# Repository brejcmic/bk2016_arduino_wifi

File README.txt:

Arduino project
Student: Poznicek

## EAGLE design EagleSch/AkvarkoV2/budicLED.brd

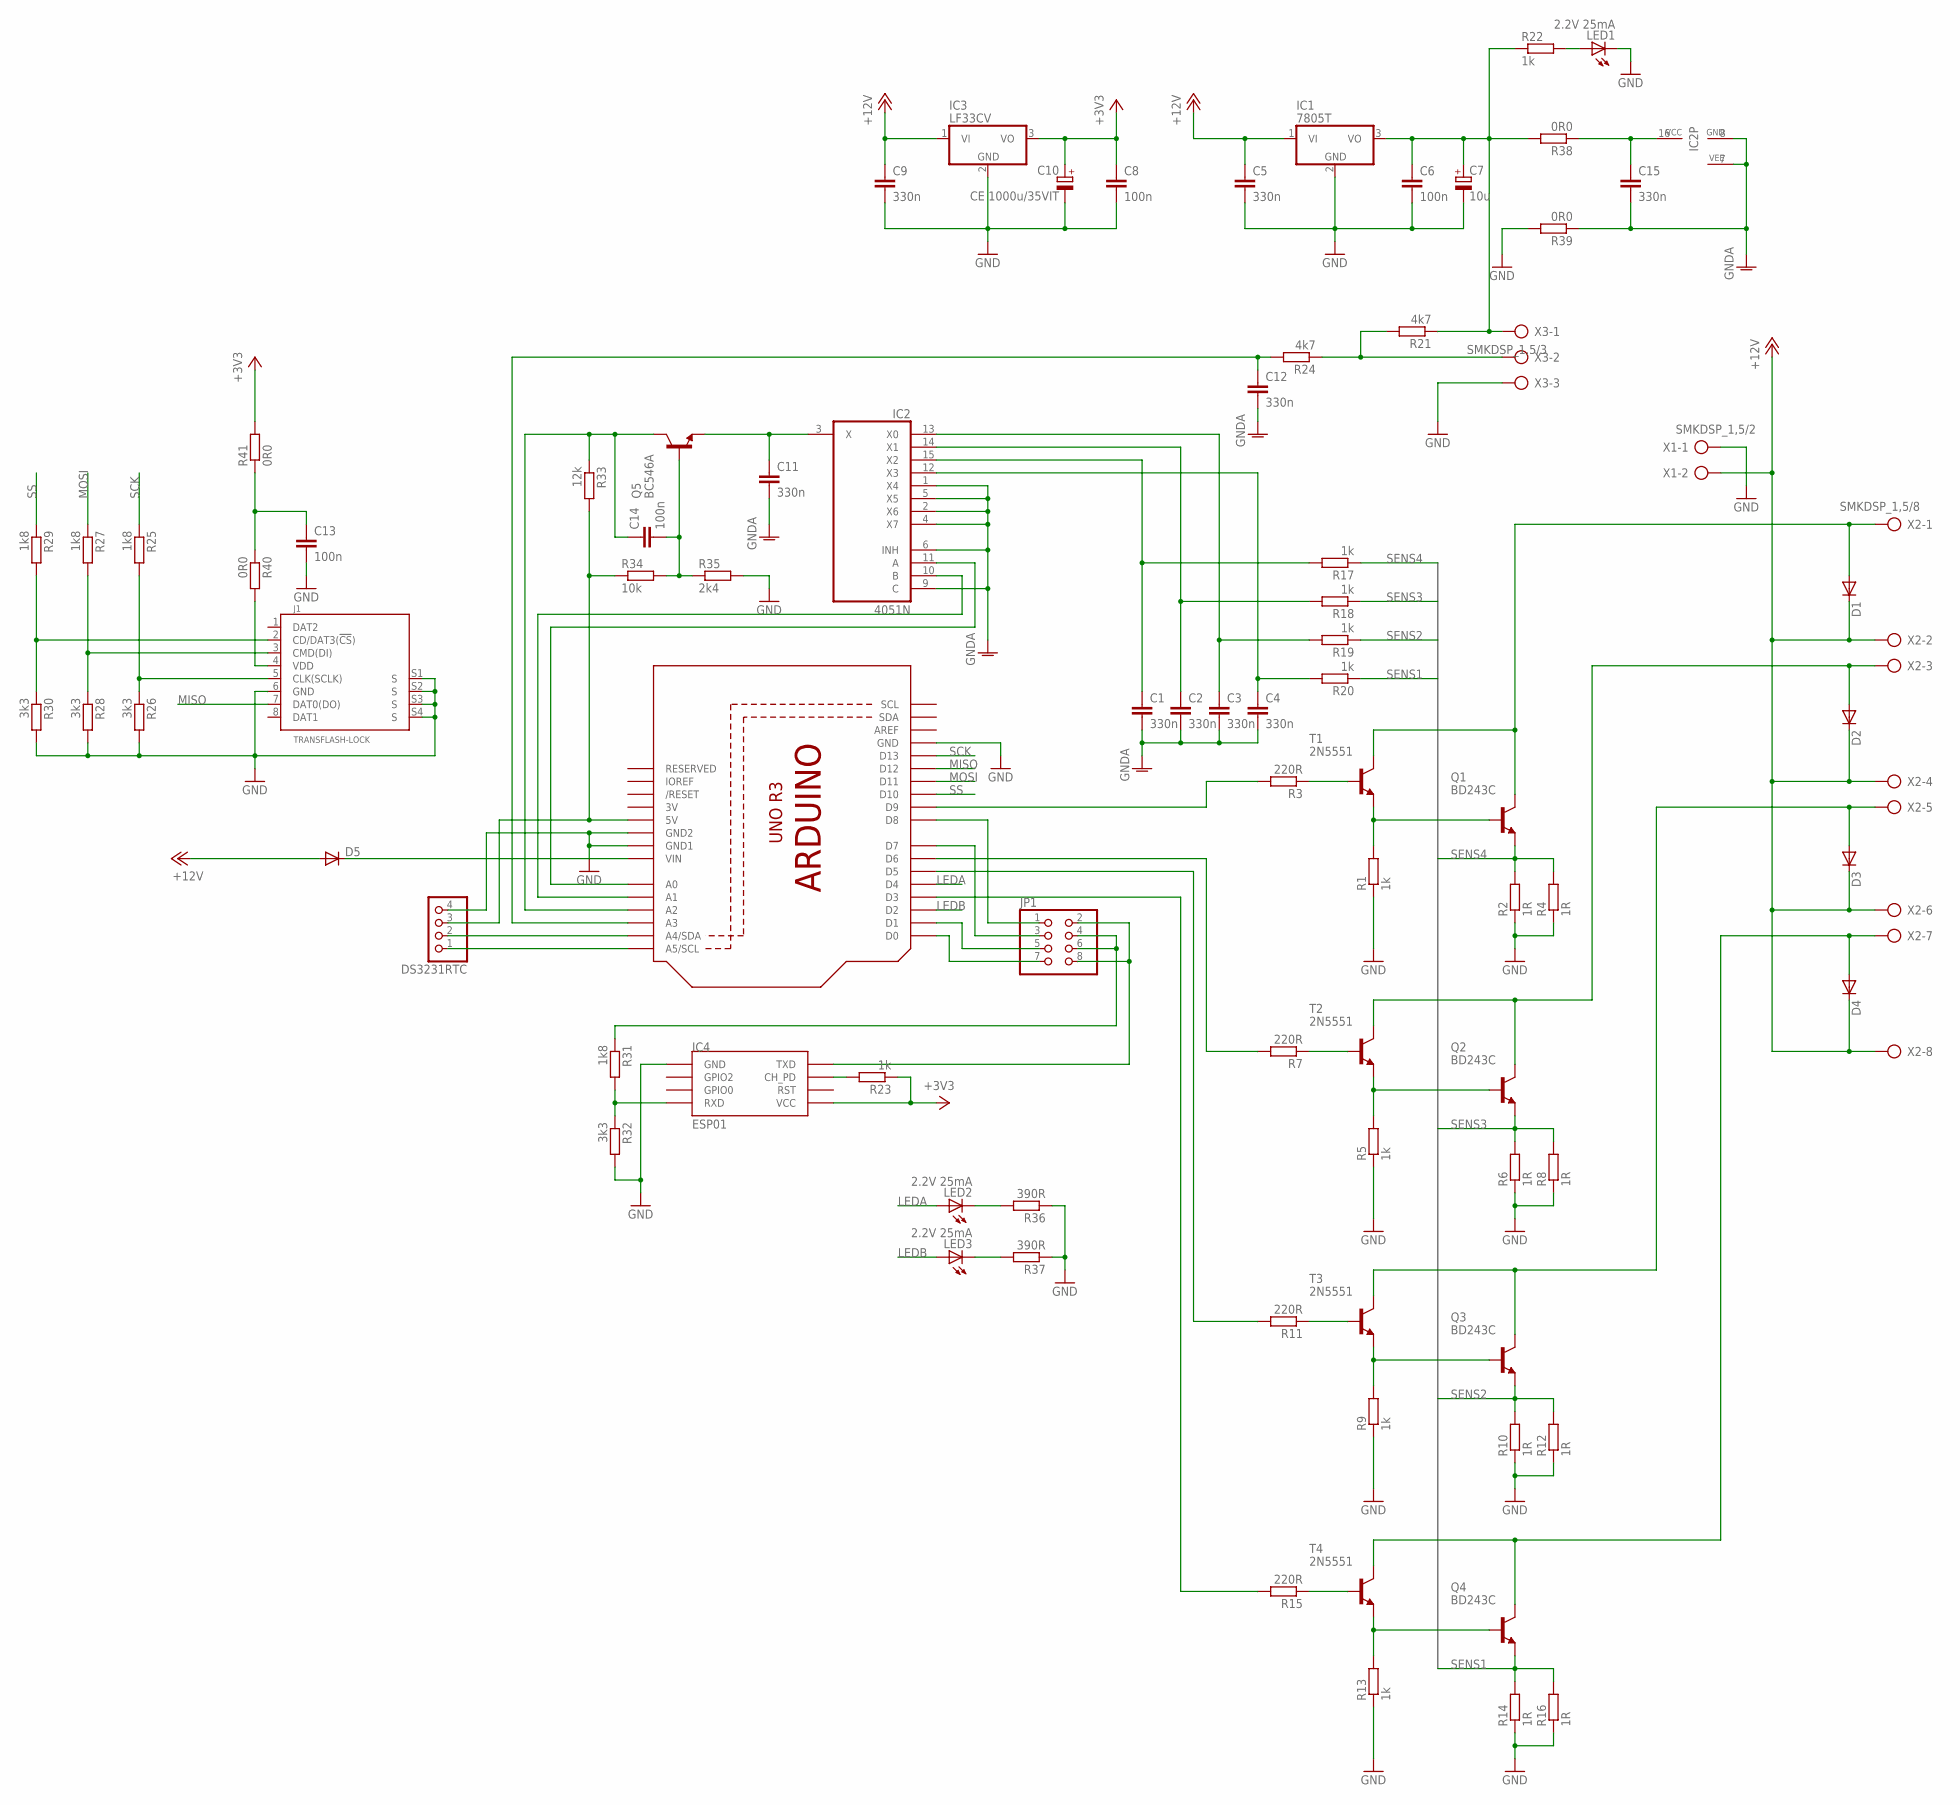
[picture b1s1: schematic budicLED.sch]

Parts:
C1, C2, C3, C4, C5, C9, C11, C12, C15: 330n; C1206K
C6, C8, C13, C14: 100n; C1206K
C7: 10u; E5-10,5
C10: CE 1000u/35VIT; E5-10,5
D1, D2, D3, D4: DIODE-DO201-15; DO201-15
D5: DIODE-MELF-MLL41; MELF-MLL41
DS3231RTC: PINHD-1X4; 1X04
IC1: 7805T; TO220H
IC2: 4051N; DIL16
IC3: LF33CV; TO220H
IC4: ESP01
J1: TRANSFLASH-LOCK; TRANSFLASH-LOCK-SOCK
JP1: PINHD-2X4; 2X04
LED1, LED2, LED3: 2.2V 25mA; LED3MM
Q1, Q2, Q3, Q4: BD243C; TO220
Q5: BC546A; TO92-EBC
R1, R5, R9, R13: 1k; 0207/12
R2, R4, R6, R8, R10, R12, R14, R16: 1R; 0411/15
R3, R7, R11, R15: 220R; 0207/12
R17, R18, R19, R20, R22, R23: 1k; R0805
R21: 4k7; 0207/12
R24: 4k7; 0207/15
R25, R27, R29, R31: 1k8; 0207/12
R26, R28, R30, R32: 3k3; 0207/12
R33: 12k; 0207/12
R34: 10k; 0207/12
R35: 2k4; 0207/12
R36, R37: 390R; 0207/12
R38: 0R0; 0207/15
R39, R40, R41: 0R0; 0207/12
T1, T2, T3, T4: 2N5551; TO92-CBE
U1: ARDUINOR3-DIMENSION; ARDUINOR3
X1: SMKDSP_1,5/2
X2: SMKDSP_1,5/8
X3: SMKDSP_1,5/3

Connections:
3V: U1.3V
+3V3: C8.1, C10.+, IC3.3 (VO), IC4.VCC, R23.1, R41.2
+12V: C5.1, C9.1, D1.C, D2.C, D3.C, D4.C, D5.A, IC1.1 (VI), IC3.1 (VI), X1.2, X2.2, X2.4, X2.6, X2.8
GND: C5.2, C6.2, C7.-, C8.2, C9.2, C10.-, C13.2, DS3231RTC.4, IC1.2 (GND), IC3.2 (GND), IC4.GND, J1.6 (GND), J1.S1 (S), J1.S2 (S), J1.S3 (S), J1.S4 (S), LED1.K (C), R1.1, R2.1, R4.1, R5.1, R6.1, R8.1, R9.1, R10.1, R12.1, R13.1, R14.1, R16.1, R26.2, R28.2, R30.2, R32.2, R35.2, R36.1, R37.1, R39.2, U1.GND, U1.GND1, U1.GND2, X1.1, X3.3
GNDA: C1.2, C2.2, C3.2, C4.2, C11.2, C12.2, C15.2, IC2.1 (X4), IC2.2 (X6), IC2.4 (X7), IC2.5 (X5), IC2.6 (INH), IC2.7 (VEE), IC2.8 (GND), IC2.9 (C), R39.1
LEDA: LED2.A, U1.D4
LEDB: LED3.A, U1.D2
MISO: J1.7 (DAT0(DO)), U1.D12
MOSI: R27.1, U1.D11
unnamed: Q1.1 (B), R1.2, T1.E
unnamed: D1.A, Q1.2 (C), T1.C, X2.1
unnamed: R3.1, T1.B
unnamed: D2.A, Q2.2 (C), T2.C, X2.3
unnamed: D3.A, Q3.2 (C), T3.C, X2.5
unnamed: Q2.1 (B), R5.2, T2.E
unnamed: D4.A, Q4.2 (C), T4.C, X2.7
unnamed: R7.1, T2.B
unnamed: Q3.1 (B), R9.2, T3.E
unnamed: R21.2, R24.1, X3.2
unnamed: R11.1, T3.B
unnamed: Q4.1 (B), R13.2, T4.E
unnamed: DS3231RTC.1, U1.A5 (A5/SCL)
unnamed: R15.1, T4.B
unnamed: R11.2, U1.D5
unnamed: R3.2, U1.D9
unnamed: IC4.CH_PD, R23.2
unnamed: C14.1, Q5.C, R33.1, U1.A2
unnamed: C14.2, Q5.B, R34.2, R35.1
unnamed: IC4.TX (TXD), JP1.2, JP1.8
unnamed: C12.1, R24.2, U1.A3
unnamed: R7.2, U1.D6
unnamed: C6.1, C7.+, IC1.3 (VO), R21.1, R22.1, R38.2, X3.1
unnamed: DS3231RTC.2, U1.A4 (A4/SDA)
unnamed: JP1.4, JP1.6, R31.1
unnamed: IC2.11 (A), U1.A0
unnamed: LED1.A, R22.2
unnamed: JP1.3, U1.D7
unnamed: C1.1, IC2.15 (X2), R17.2
unnamed: C2.1, IC2.14 (X1), R18.2
unnamed: C3.1, IC2.13 (X0), R19.2
unnamed: J1.5 (CLK(SCLK)), R25.2, R26.1
unnamed: C4.1, IC2.12 (X3), R20.2
unnamed: IC2.10 (B), U1.A1
unnamed: R15.2, U1.D3
unnamed: J1.3 (CMD(DI)), R27.2, R28.1
unnamed: J1.2 (CD/DAT3(!CS!)), R29.2, R30.1
unnamed: JP1.5, U1.D1
unnamed: IC4.RX (RXD), R31.2, R32.1
unnamed: C11.1, IC2.3 (X), Q5.E
unnamed: JP1.7, U1.D0
unnamed: JP1.1, U1.D8
unnamed: LED2.K (C), R36.2
unnamed: DS3231RTC.3, R33.2, R34.1, U1.5V
unnamed: LED3.K (C), R37.2
unnamed: C15.1, IC2.16 (VCC), R38.1
unnamed: J1.4 (VDD), R40.2
unnamed: D5.C, U1.VIN
unnamed: C13.1, R40.1, R41.1
SCK: R25.1, U1.D13
SENS1: Q4.3 (E), R14.2, R16.2, R20.1
SENS2: Q3.3 (E), R10.2, R12.2, R19.1
SENS3: Q2.3 (E), R6.2, R8.2, R18.1
SENS4: Q1.3 (E), R2.2, R4.2, R17.1
SS: R29.1, U1.D10

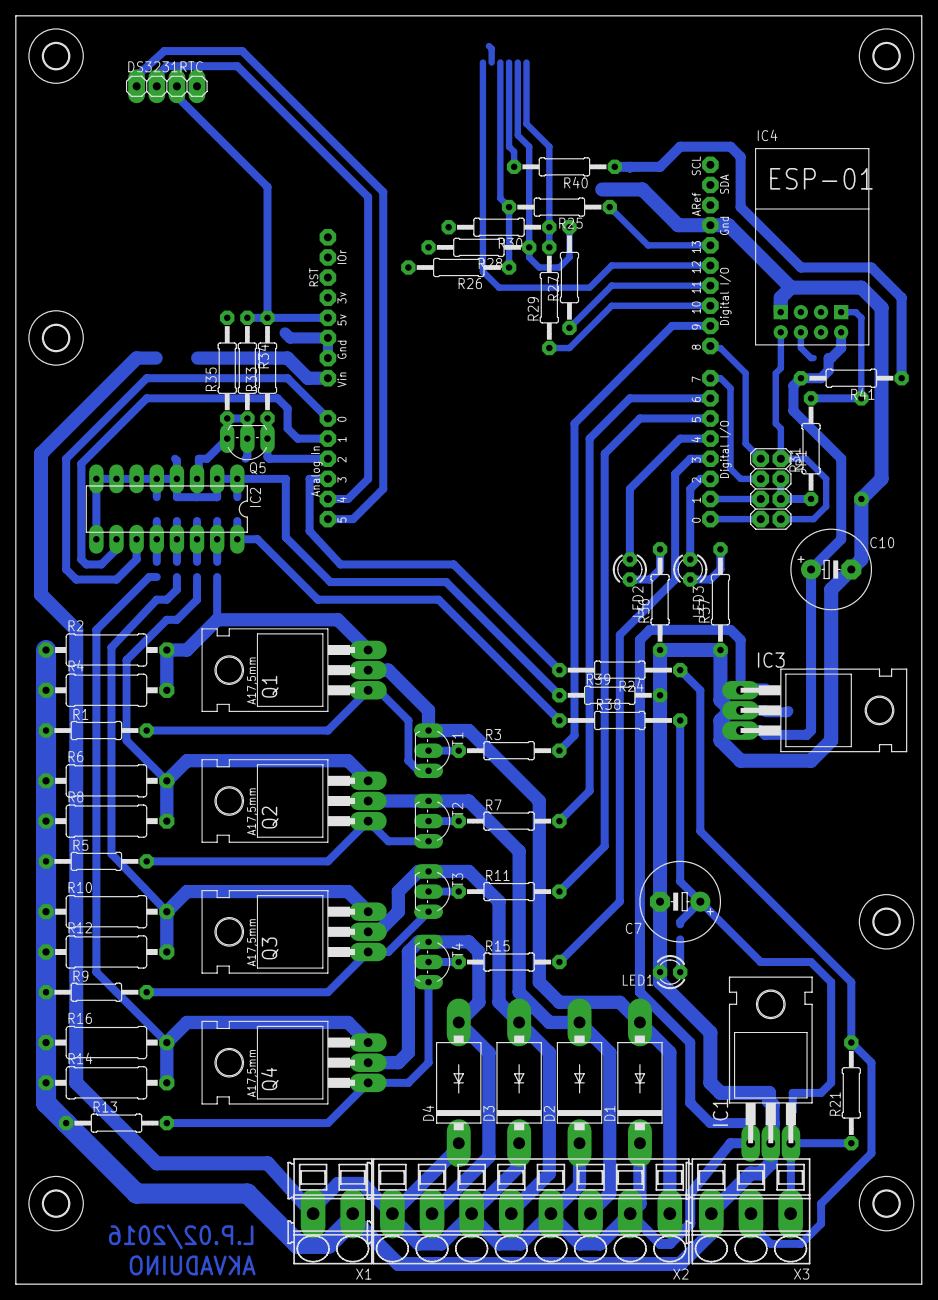
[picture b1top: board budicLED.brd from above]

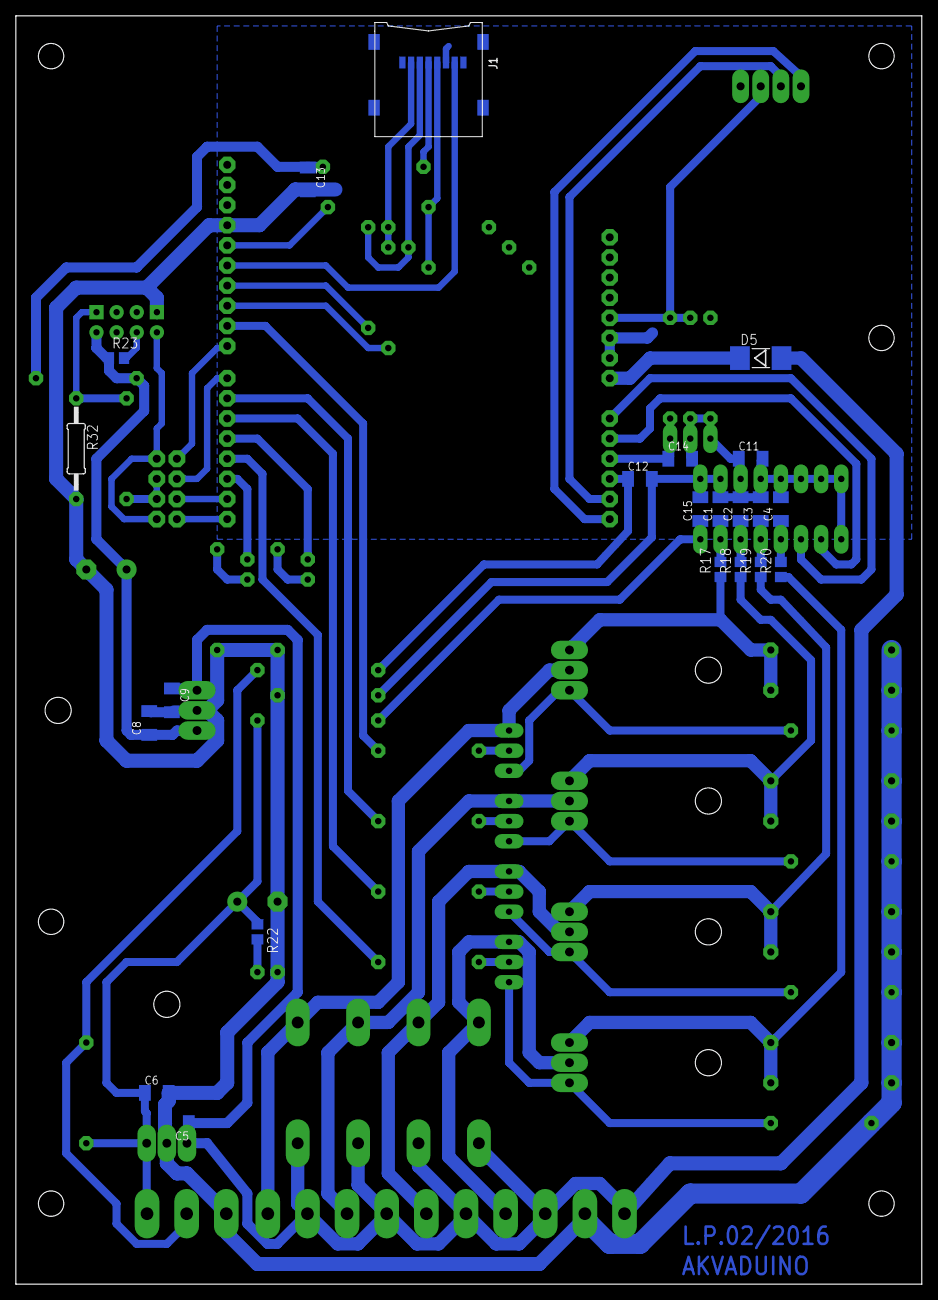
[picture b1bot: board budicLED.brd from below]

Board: 2 copper layers, 114.3 x 160.0 mm, 90 parts (22 on the bottom side), 63 nets.

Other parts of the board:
U$1, U$2, U$3, U$4, U$5, U$6: 3,2

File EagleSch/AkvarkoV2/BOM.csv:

"Qty";"Value";"Device";"Package";"Parts";"Description";"";
"4";"";"DIODE-DO201-15";"DO201-15";"D1, D2, D3, D4";"DIODE";"";
"1";"";"PINHD-1X4";"1X04";"DS3231RTC";"PIN HEADER";"";
"1";"";"PINHD-2X4";"2X04";"JP1";"PIN HEADER";"";
"3";"0R0";"R-EU_0207/12";"0207/12";"R39, R40, R41";"RESISTOR, European symbol";"";
"1";"0R0";"R-EU_0207/15";"0207/15";"R38";"RESISTOR, European symbol";"";
"4";"100n";"C-EUC1206K";"C1206K";"C6, C8, C9, C13";"CAPACITOR, European symbol";"";
"3";"10k";"R-EU_0207/12";"0207/12";"R33, R34, R35";"RESISTOR, European symbol";"";
"1";"10u";"CPOL-EUE5-10.5";"E5-10,5";"C7";"POLARIZED CAPACITOR, European symbol";"";
"8";"1R";"R-EU_0411/15";"0411/15";"R2, R4, R6, R8, R10, R12, R14, R16";"RESISTOR, European symbol";"";
"4";"1k";"R-EU_0207/12";"0207/12";"R1, R5, R9, R13";"RESISTOR, European symbol";"";
"4";"1k";"R-EU_R0805";"R0805";"R17, R18, R19, R20";"RESISTOR, European symbol";"";
"4";"1k8";"R-EU_0207/12";"0207/12";"R25, R27, R29, R31";"RESISTOR, European symbol";"";
"3";"2.2V 25mA";"LED3MM";"LED3MM";"LED1, LED2, LED3";"LED";"";
"4";"220R";"R-EU_0207/12";"0207/12";"R3, R7, R11, R15";"RESISTOR, European symbol";"";
"4";"2N5551";"2N5551-NPN-TO92-CBE";"TO92-CBE";"T1, T2, T3, T4";"NPN Transistror";"";
"9";"330n";"C-EUC1206K";"C1206K";"C1, C2, C3, C4, C5, C11, C12, C14, C15";"CAPACITOR, European symbol";"";
"2";"390R";"R-EU_0207/12";"0207/12";"R36, R37";"RESISTOR, European symbol";"";
"1";"390R";"R-EU_R0805";"R0805";"R22";"RESISTOR, European symbol";"";
"4";"3k3";"R-EU_0207/12";"0207/12";"R26, R28, R30, R32";"RESISTOR, European symbol";"";
"1";"4051N";"4051N";"DIL16";"IC2";"8-channel ANALOG MULTIPLEXER";"";
"1";"4k7";"R-EU_0207/12";"0207/12";"R21";"RESISTOR, European symbol";"";
"1";"4k7";"R-EU_0207/15";"0207/15";"R24";"RESISTOR, European symbol";"";
"1";"4k7";"R-EU_R0805";"R0805";"R23";"RESISTOR, European symbol";"";
"1";"7805T";"7805T";"TO220H";"IC1";"Positive VOLTAGE REGULATOR";"";
"1";"ARDUINOR3-DIMENSION";"ARDUINOR3-DIMENSION";"ARDUINOR3";"U1";"This is a new object for the new Arduino R3 - with extra pins that you may want to use (such as IOref, and duplicated A4/A5";"";
"1";"BC546A";"BC546A";"TO92-EBC";"Q5";"NPN Transistor";"";
"4";"BD243C";"-NPN-TO220";"TO220";"Q1, Q2, Q3, Q4";"NPN Transistror";"";
"1";"CE 1000u/35VIT";"CPOL-EUE5-10.5";"E5-10,5";"C10";"POLARIZED CAPACITOR, European symbol";"";
"1";"ESP01";"ESP01";"ESP01";"IC4";"ESP8266 Wifi module 01";"";
"1";"LF33CV";"7805T";"TO220H";"IC3";"Positive VOLTAGE REGULATOR";"";
"1";"SMKDSP_1,5/2";"SMKDSP_1,5/2";"SMKDSP_1,5/2";"X1";"Printklemme, Nennstrom: 17,5 A, Bemessungsspannung: 250 V, Raster: 5,0 mm";"";
"1";"SMKDSP_1,5/3";"SMKDSP_1,5/3";"SMKDSP_1,5/3";"X3";"Printklemme, Nennstrom: 17,5 A, Bemessungsspannung: 250 V, Raster: 5,0 mm";"";
"1";"SMKDSP_1,5/8";"SMKDSP_1,5/8";"SMKDSP_1,5/8";"X2";"Printklemme, Nennstrom: 17,5 A, Bemessungsspannung: 250 V, Raster: 5,0 mm";"";
"1";"TRANSFLASH-LOCK";"TRANSFLASH-LOCK";"TRANSFLASH-LOCK-SOCK";"J1";"TransFlash TF Micro SD Card Socket Adapter";"";

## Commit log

2016-03-14 Poznamka v README
2016-03-14 Manualy a zaklad seriove komunikace
2016-03-14 Pridano vraceni html stranky.
2016-03-15 Funkcni kod. Lze se pripojit na zarizeni pres web browser. Na obrazovce se vypise Ahoj.
2016-03-16 Pridan priklad html stranky od Honzy
2016-03-17 Zmena vykreslovani webovky, odzkouseno. Zapis webu do String.
2016-03-17 Rozpracovano nasobne vraceni ruznych webovych stranek
2016-03-18 Funkcni kod, ktery pres webovy prohlizec rozsveci a zhasina ledku na pinu 7.
2016-03-18 Stranky byly pojmenovany pomoci enum.
2016-03-21 Rozpracovany stavovy automat odesilani html stranky.
2016-03-22 Stale nefunguje odesilani stranky. Velikost pameti vyhovuje.
2016-03-23 Konecne trochu funkcni htmlMonitor.
2016-03-23 htmlMonitor je plne funkcni. Lze odesilat stranku do velikosti 2k. Odzkouseno
2016-03-24 - predelano casovani udalosti, nyni pomoci "com_delay" - doplneny ochrany jako WATCHDOG - smazany prebytecne lokalni promenne - prejmenovany funkce monitoru - odzkouseno, funkcni
2016-03-24 Pridan popis HTTP 1.1
2016-03-26 Zmenena funkce nalezeni retezce. Nyni se retezec hleda v poslednich 8 znacich.
2016-03-27 Funkcni servisni log a predelana koncepce hledani retezcu. Vystup obou seriovych linek se zapisuje do FIFO, ve kterem se nasledne hleda retezec.
2016-03-28 Predelana inicializace pripojeni k wifi siti. Inicializace rozdelena do dvou funkci, ktere lze volat samostatne. Prvni inicializuje servisni linku, druha inicializuje komunikaci s esp8266. Odzkouseno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
2016-03-28 Funkcni rozdelelni zpravy do vice paketu.
2016-03-30 Verze zakladove desky akvaduino pred upravami
2016-03-30 Pridan slot pro SD kartu, odstraneny signalizacni diody.
2016-03-31 Přidán datasheet ESP8266
2016-03-31 Na DPS: - upraveno napajeni - zmenena pouzdra rezistoru u SD karty - seriova linka vyvedena na kolikovou listu - zvetsena sirka spoje GND, doplnen jeden filtracni kapacitor k SD slotu
2016-03-31 DPS pred vyrobou, nutna kontrola rozmeru.
2016-04-01 DPS: - pridany LED, - dratove propojky nahrazeny reszistory 0R0, - doplnena rozlita med, - pridan zesilovaci prvek (tranzistor) k AD prevodnikum od snimani proudu ve vykonovem obvodu, - pridano nekol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
2016-04-01 DPS: - posilena tloustka vykonove zeme a privodu napajeni k Arduino UNO
2016-04-02 DPS: - RTC modul obracen o 90°, jinak se nevejde do krabicky.
2016-04-02 Pripravena vyrobni data.
2016-04-05 Doplnen BOM
2016-04-06 DPS: - vytvorena objednavka soucastek v GME
2016-04-06 Odstraneny zalohovaci soubory Eaglu
2016-04-06 Pridan gitignore
2016-04-14 DPS: - opraven chybejici propoj - opraveno zrcadleni soucastek
2016-04-15 Ostranen soubor epf a doplneny popisky vyvodu u diod.
2016-04-20 - pridelany PWM signaly - opravena chyba v cekani na potvrzeni odeslani packetu
2016-04-20 - upraveny hodnoty odporu u zesilovace napeti z bocniku - pridana dioda do napajeciho vstupu ARDUINO
2016-04-20 - odzkouseny zapis na SD kartu
2016-04-21 Program: - odzkouseny RTC
2016-04-22 DPS: - opravena chybna cesta u rezistoru R1
2016-04-25 Program: - snizeny pametove naroky na RAM - pocatek implementace SD
2016-04-25 Program: - cteni webky z SD karty
2016-04-27 Program: - odladěno vysilani webu z SD karty
2016-04-28 Program: -oupraveno preposilani posledniho packetu -neodzkouseno
2016-05-04 Program: - zmenena operace s nacitanim SD karty = presunuto do vlastni funkce - presunuty vsechny funkce pro ovladani HW
2016-05-04 Program: - snizena velikost prostoru, ktery zabiraly globalni promenne
2016-05-04 testovani
2016-05-04 Program x nefunguje komunikace s esp2866 x spatne se odesilaji prikazy
2016-05-04 Program: - opravena chyba predchoziho commitu
2016-05-04 Program: - zmenena rychlost - odzkousena komunikace
